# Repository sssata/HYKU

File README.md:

<p align="center">
  
  <br>
  
</p>

[Store Link](https://www.tindie.com/products/kappachino/hyku-tablet/)

## First Time Setup Instructions, [Updated for HYKU Configurator v0.6](https://github.com/sssata/HYKU/releases/tag/v0.6.0)

1. Download HYKU_Configurator.exe from [here](https://github.com/sssata/HYKU/releases/tag/v0.6.0).
2. Plug in tablet with a USB-C cable. The LED should light up in a bright rainbow.
3. Deactivate tablet by holding down the keyswitchs for 1 second. The LED should turn blue.
4. Open the HYKU Configurator and open the Tools tab. Ensure tablet is recognized by the program with the "Connected" indicator at the bottom left.
5. Click Fetch Releases button, select latest version (v0.5 as of now), and press Update.
6. After Update completes, the tablet will need to be re-calibrated.
7. To Calibrate, position arm in a straight line as shown in image and press calibrate.
  
2. Reactivate tablet by holding down the keyswitchs for 1 second. The LED should turn bright rainbow.

## Configurator Usage Instructions
1. Configure tablet screen area and tablet area by entering values in the Area Settings tab.
2. Ensure Tablet is plugged in and recognized by the program with the "Connected" indicator at the bottom left.
3. Press the Upload button to apply settings and upload them to the tablet.

## Multi Monitor Instructions

# What is it?

The HYKU Tablet is a novel drawing tablet-style input device designed from the ground up for osu!.

**Image Below Links to Video:**

## Why HYKU?

The goal of the HYKU is to create a pen tablet that is optimized for low latency. Most drawing tablets currently available offer polling rates below 200 Hz and have some level of hardware filtering that further decreases responsiveness, while the HYKU provides 600 Hz of raw sensor output.

## Using the HYKU

**The HYKU tablet is plug and play and requires no drivers**. The screen and tablet area settings are written and saved on the tablet through the HYKU Configurator utility.

The configurator utility allows:
- Setting Screen area and Tablet area
- Setting cursor smoothing

The tablet features a single button: 

### Download

The latest version of the configurator program can be found in [Releases](https://github.com/sssata/HYKU/releases).

## What's in the Box
- 1x HYKU Tablet, fully assembled
- 1x Tablet Pen, Removable 
- 1x 2m USB Type C to USB Type A Cable

## Tablet Specs

- **Polling Rate:** 600 Hz
- **Max Tablet Area:** Approx. 100mm x 80mm
- **Max Physical Resolution:** Approx. 0.091mm
- **Connector:** USB-C
- **Hot Swappable Switch**
- **OS Compatibility:** Windows 10 64-bit

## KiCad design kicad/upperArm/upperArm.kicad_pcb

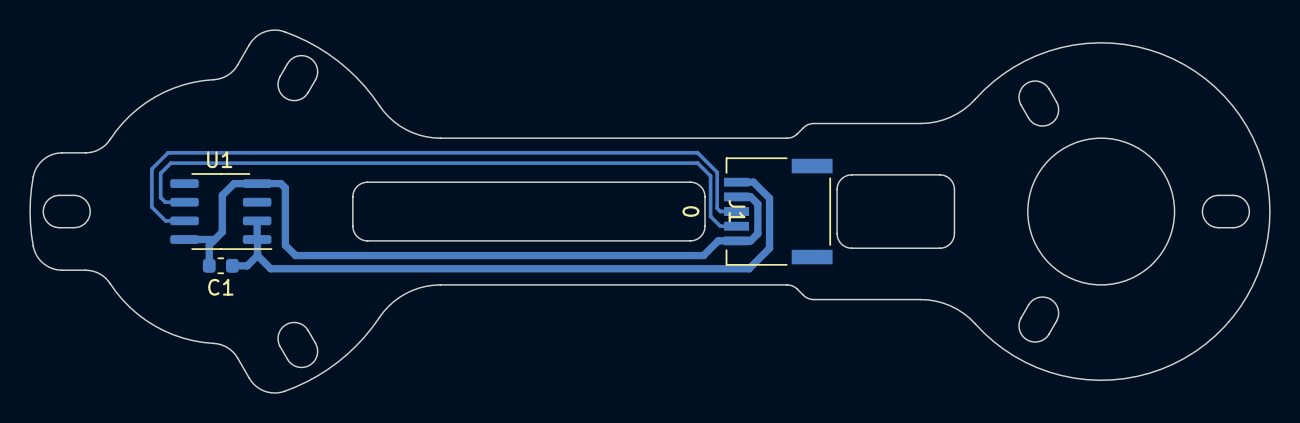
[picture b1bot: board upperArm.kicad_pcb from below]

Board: 2 copper layers, 84.5 x 24.7 mm, 3 parts (3 on the bottom side), 4 nets.

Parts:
C1: 100nF; C_0603_1608Metric
J1: 0; SM05B-NSHSS-TBLFSN
U1: AS5600; SOIC-8_3.9x4.9mm_P1.27mm

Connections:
+3V3: C1.1, J1.5, U1.1, U1.2
GND: C1.2, J1.1, J1.4, U1.4, U1.8
SCL: J1.3, U1.7
SDA2: J1.2, U1.6

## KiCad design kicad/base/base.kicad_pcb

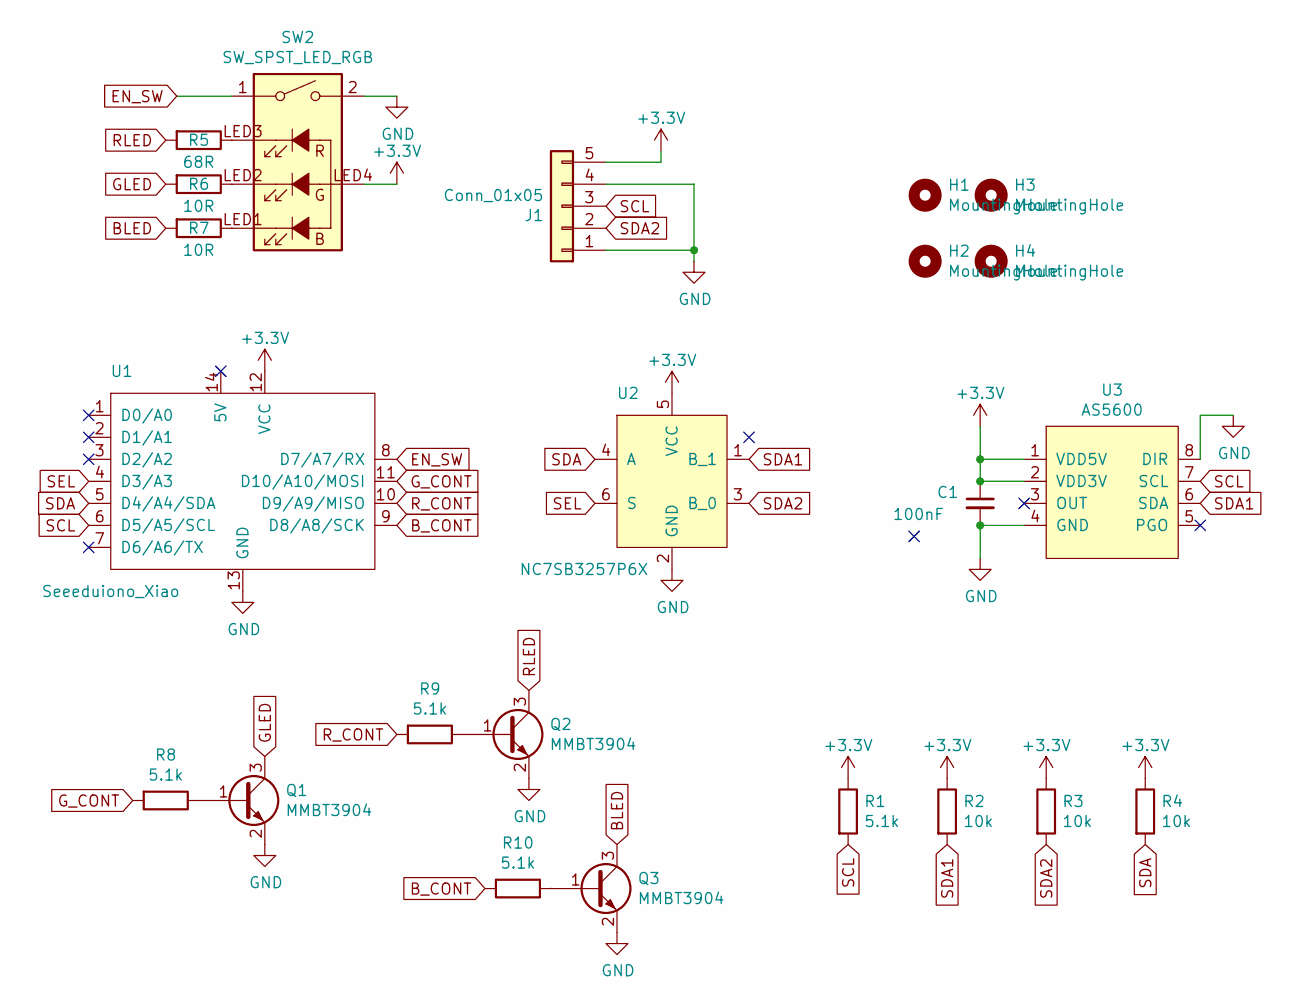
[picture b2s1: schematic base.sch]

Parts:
C1: 100nF; C_0805_2012Metric; LCSC C49678
H1, H2, H3, H4: MountingHole; MountingHole_3.2mm_M3_Pad_Via
J1: Conn_01x05; SM05B-NSHSS-TBLFSN
Q1, Q2, Q3: MMBT3904; SOT-23; LCSC C20526
R1, R8, R9, R10: 5.1k; R_0805_2012Metric; LCSC C27834
R2, R3, R4: 10k; R_0805_2012Metric; LCSC C17414
R5: 68R; R_0805_2012Metric; LCSC C17802
R6, R7: 10R; R_0805_2012Metric; LCSC C17415
SW2: SW_SPST_LED_RGB; Kailh_socket_MX_SMD_RGB
U1: Seeeduiono_Xiao; Seeeduino_Xiao
U2: NC7SB3257P6X; SOT-363_SC-70-6
U3: AS5600; SOIC-8_3.9x4.9mm_P1.27mm

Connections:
+3V3: C1.1, J1.5, R1.1, R2.1, R3.1, R4.1, SW2.LED4, U1.12 (VCC), U2.5 (VCC), U3.1 (VDD5V), U3.2 (VDD3V)
BLED: Q3.3 (C), R7.2
B_CONT: R10.2, U1.9 (D8/A8/SCK)
EN_SW: SW2.1, U1.8 (D7/A7/RX)
GLED: Q1.3 (C), R6.2
GND: C1.2, J1.1, J1.4, Q1.2 (E), Q2.2 (E), Q3.2 (E), SW2.2, U1.13 (GND), U2.2 (GND), U3.4 (GND), U3.8 (DIR)
G_CONT: R8.2, U1.11 (D10/A10/MOSI)
unnamed: Q1.1 (B), R8.1
unnamed: Q2.1 (B), R9.1
unnamed: Q3.1 (B), R10.1
unnamed: R5.1, SW2.LED3
unnamed: R6.1, SW2.LED2
unnamed: R7.1, SW2.LED1
RLED: Q2.3 (C), R5.2
R_CONT: R9.2, U1.10 (D9/A9/MISO)
SCL: J1.3, R1.2, U1.6 (D5/A5/SCL), U3.7 (SCL)
SDA: R4.2, U1.5 (D4/A4/SDA), U2.4 (A)
SDA1: R2.2, U2.1 (B_1), U3.6 (SDA)
SDA2: J1.2, R3.2, U2.3 (B_0)
SEL: U1.4 (D3/A3), U2.6 (S)

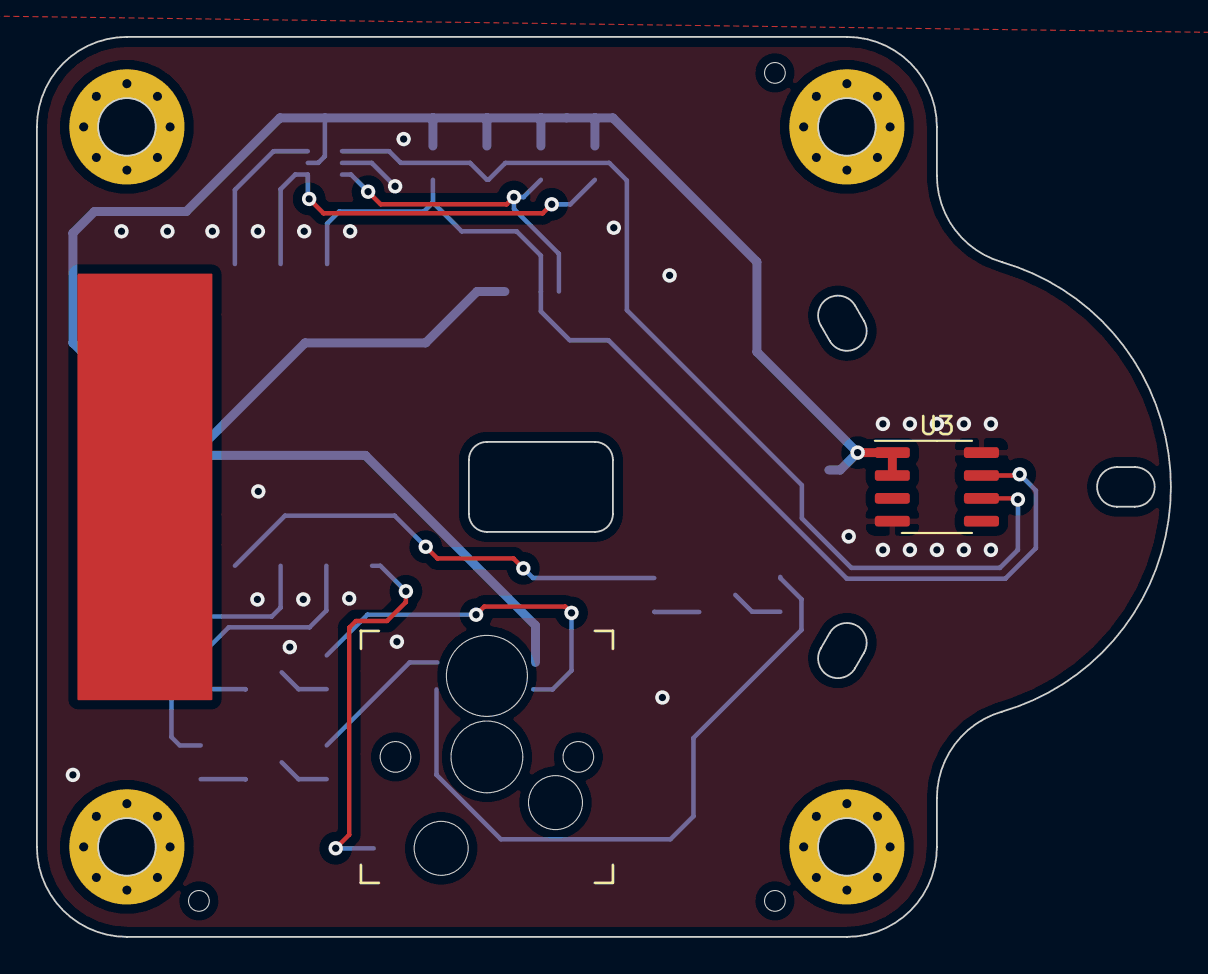
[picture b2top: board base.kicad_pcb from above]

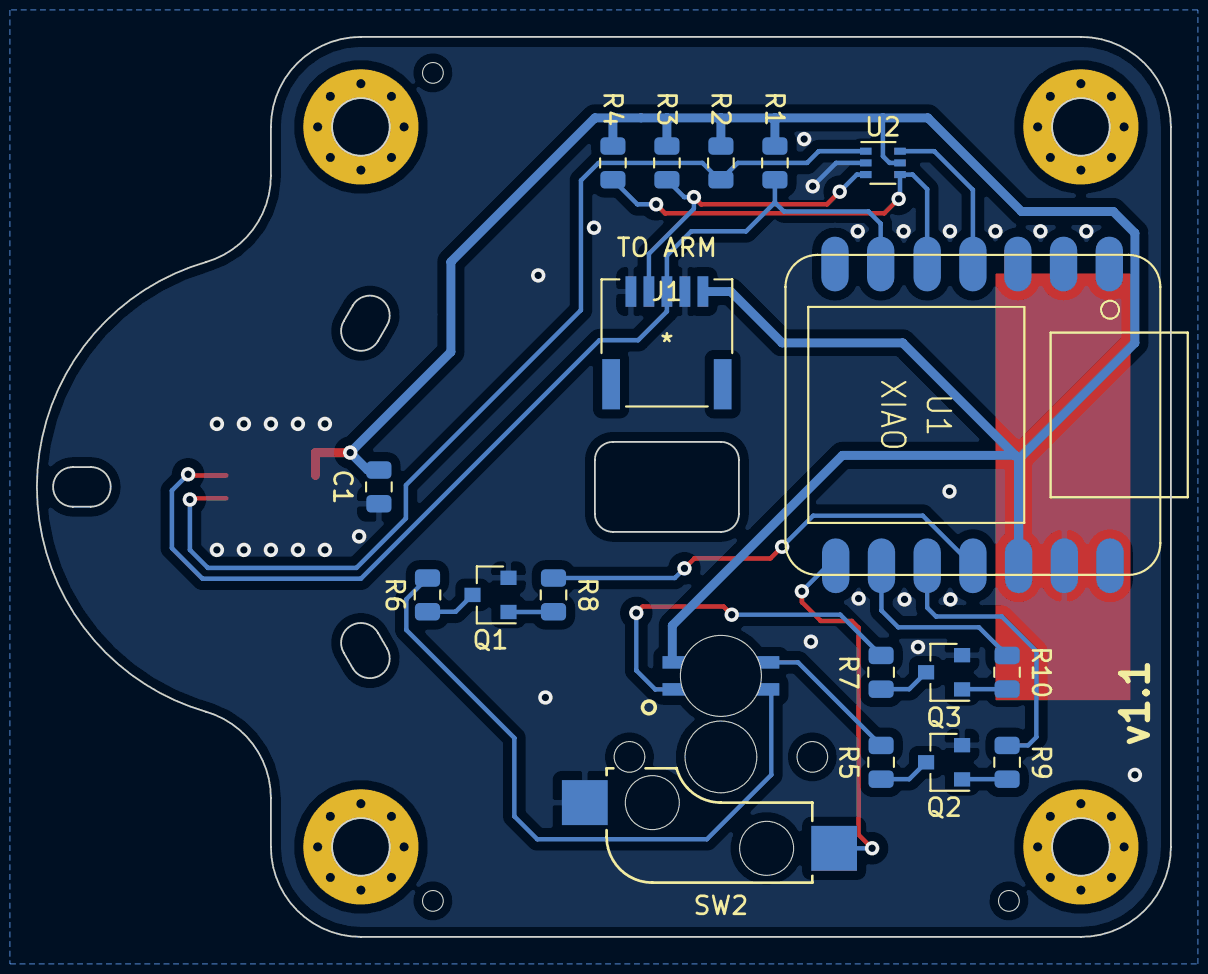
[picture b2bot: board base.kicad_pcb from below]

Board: 2 copper layers, 63.0 x 50.0 mm, 23 parts (17 on the bottom side), 20 nets.

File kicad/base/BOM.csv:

Comment,Designator,Footprint,LCSC
100nF,C1,Capacitor_SMD:C_0805_2012Metric,C49678
MMBT3904,"Q1,Q2,Q3",Package_TO_SOT_SMD:SOT-23,C20526
5.1k,"R1,R8,R9,R10",Resistor_SMD:R_0805_2012Metric,C27834
10k,"R2,R3,R4",Resistor_SMD:R_0805_2012Metric,C17414
68R,R5,Resistor_SMD:R_0805_2012Metric,C17802
10R,"R6,R7",Resistor_SMD:R_0805_2012Metric,C17415

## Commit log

2021-12-25 added more stuff
2021-12-25 removed temp files
2021-12-25 added gitignore for solidworks
2022-01-03 updated stuff
2022-01-14 changed pen shape
2022-01-21 something
2022-01-27 added favicon
2022-02-01 Create LICENSE
2022-02-01 added exp filter config
2022-02-05 updated title of configurator
2022-02-11 Set theme jekyll-theme-tactile
2022-02-19 added left hand support, updated pcb with logo, updated pen geometry
2022-02-27 added tools tab
2022-03-08 added more info to message box
2022-03-12 added osu absolute mode

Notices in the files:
parts and their libraries:
Copyright 2021 Accelerated Designs. All rights reserved.
